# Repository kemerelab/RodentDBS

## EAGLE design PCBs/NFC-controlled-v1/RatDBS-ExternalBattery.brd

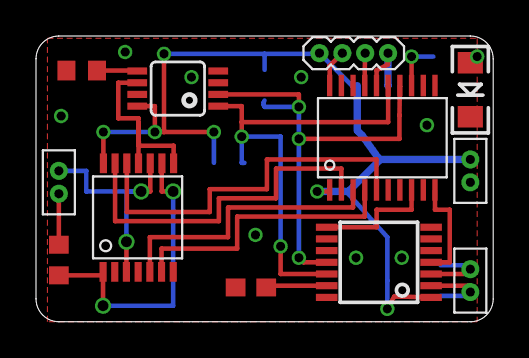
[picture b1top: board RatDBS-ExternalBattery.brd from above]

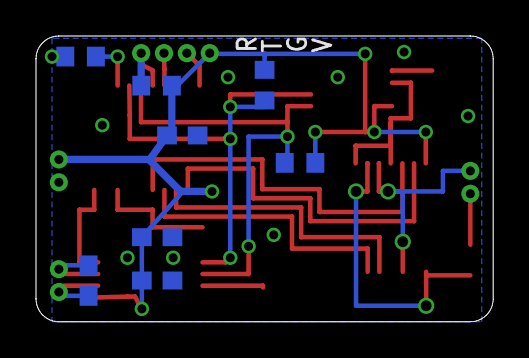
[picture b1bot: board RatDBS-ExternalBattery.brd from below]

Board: 2 copper layers, 25.4 x 15.9 mm, 20 parts (8 on the bottom side), 22 nets.

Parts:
ANT: FTSH-102; FTSH-102-DH
C1: 1µ; C0603
C2: 0.1µ; C0603
CANT: C0603
CBAT: 10µ; C0603
C_VC: 0.47µ; C0603
DS4432U+: 8_PIN
JP1: 1X04-1.27MM
LED6: GREEN; LED-1206
MSP430: MSP; 20_PIN
PWR: FTSH-102; FTSH-102-DH
R1_I2C, R2_I2C: 10k; R0603
R_INPUT_FS0: 47k; R0603
R_LED: R_LED; R0603
R_LOAD_EX: 10k; R0603
R_PULLUP_RST: 43k; R0603
STIM: FTSH-102; FTSH-102-DH
TS3A4751_0: SW; 14_PIN
U$1: RF; PW_R-PDSO-G14

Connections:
GND: C1.2, C2.2, CBAT.1, C_VC.2, DS4432U+.4, JP1.2, LED6.C, MSP430.20, PWR.P$2, R_INPUT_FS0.1, TS3A4751_0.2, TS3A4751_0.4, TS3A4751_0.7, U$1.5, U$1.6, U$1.7, U$1.9, U$1.10, U$1.14
IN1: MSP430.2, TS3A4751_0.13
IN2: MSP430.3, TS3A4751_0.5
IN3: MSP430.4, TS3A4751_0.6
IN4: MSP430.5, TS3A4751_0.12
unnamed: C_VC.1, U$1.13
unnamed: ANT.P$2, CANT.2, U$1.2
unnamed: MSP430.8, U$1.8
unnamed: R_LOAD_EX.1, STIM.P$2
unnamed: MSP430.13, R_LED.1
unnamed: MSP430.10, U$1.4
unnamed: DS4432U+.5, R_INPUT_FS0.2
unnamed: LED6.A, R_LED.2
unnamed: ANT.P$1, CANT.1, U$1.3
SCL: DS4432U+.2, MSP430.14, R2_I2C.1, U$1.11
SDA: DS4432U+.1, MSP430.15, R1_I2C.1, U$1.12
STIM_IN: DS4432U+.6, TS3A4751_0.8, TS3A4751_0.11
STIM_OUT1: R_LOAD_EX.2, TS3A4751_0.1, TS3A4751_0.9
STIM_OUT2: STIM.P$1, TS3A4751_0.3, TS3A4751_0.10
TEST: JP1.3, MSP430.17
VDD: C1.1, C2.1, CBAT.2, DS4432U+.8, JP1.1, MSP430.1, PWR.P$1, R1_I2C.2, R2_I2C.2, R_PULLUP_RST.2, TS3A4751_0.14, U$1.1
_RST: JP1.4, MSP430.16, R_PULLUP_RST.1

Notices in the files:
PCBs/NFC-controlled-v1/RatDBS-ExternalBattery.brd:
(C)2015
parts and their libraries:
SparkFun-LED: Licensing: CC v3.0 Share-Alike You are welcome to use this library for commercial purposes.
